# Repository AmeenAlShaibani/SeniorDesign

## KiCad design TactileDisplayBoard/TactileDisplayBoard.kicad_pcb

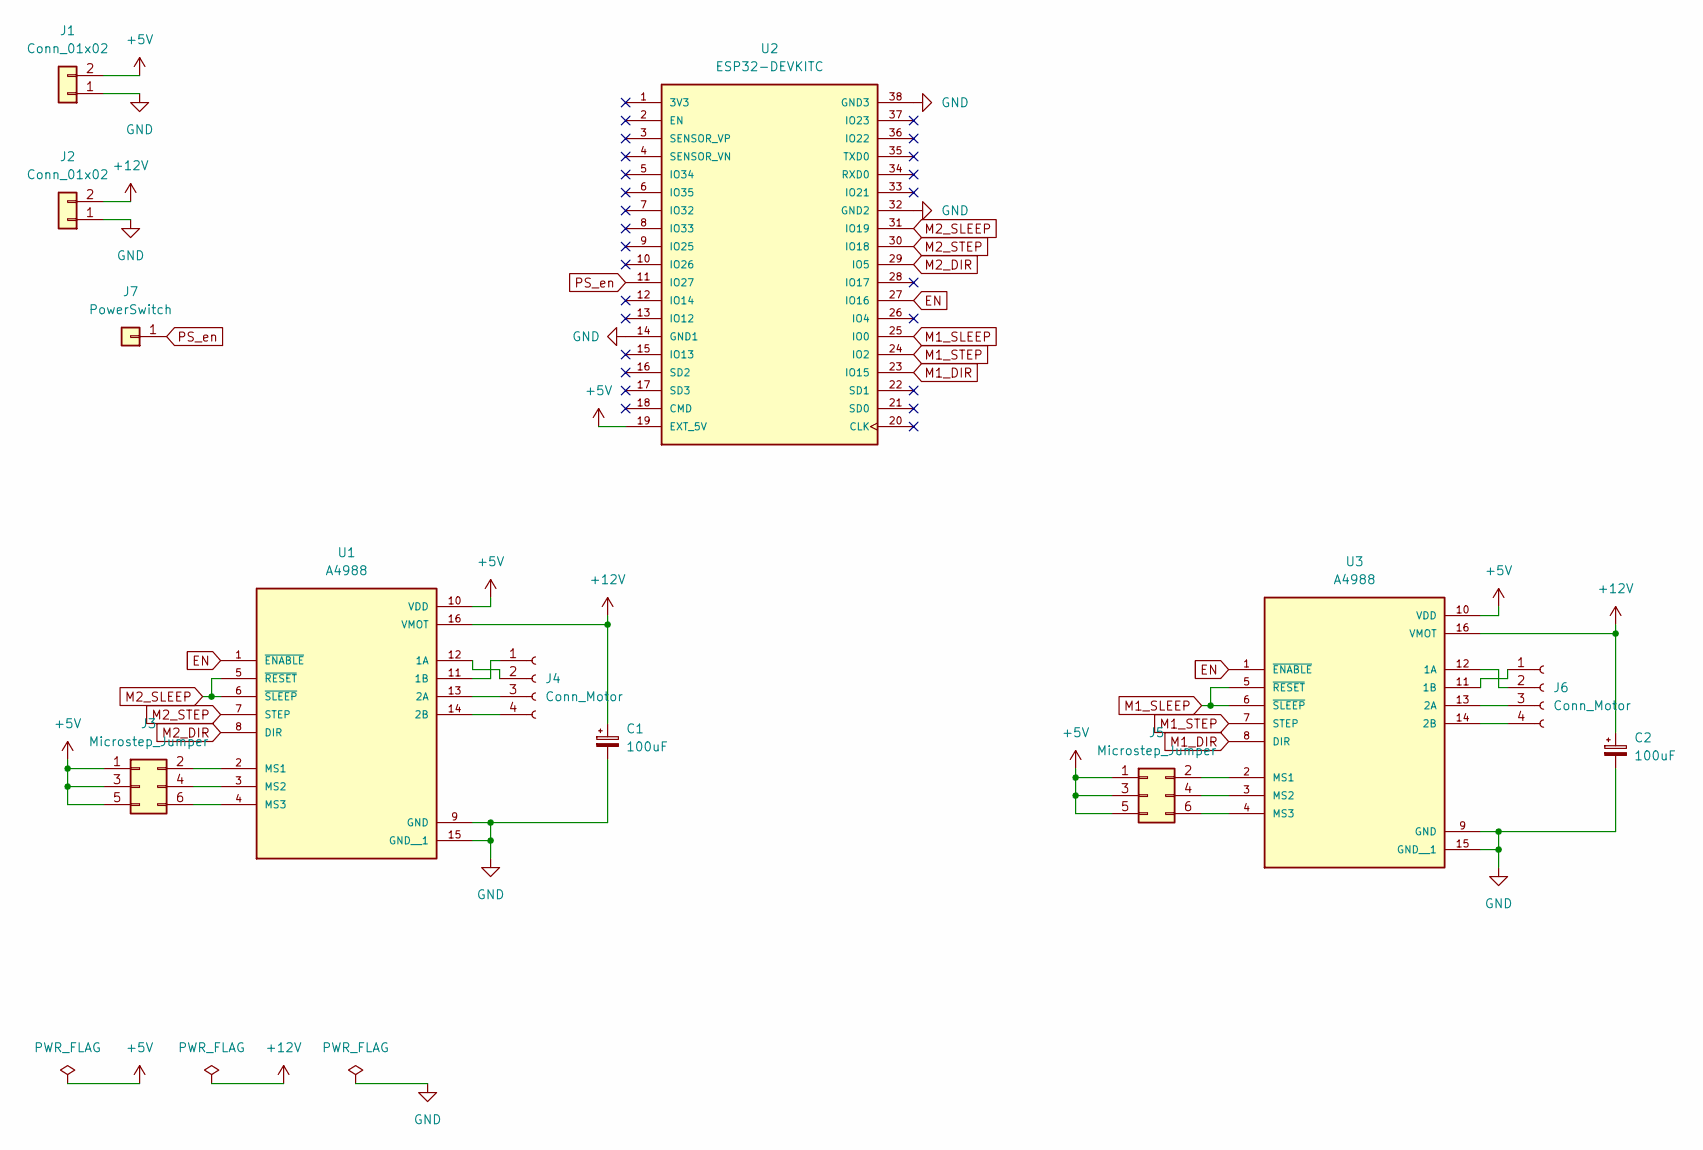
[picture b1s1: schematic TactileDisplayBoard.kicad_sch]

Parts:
C1, C2: 100uF; C_Radial_D10.0mm_H16.0mm_P5.00mm
J1, J2: Conn_01x02; BarrelJack_CUI_PJ-102AH_Horizontal
J3, J5: Microstep_Jumper; PinSocket_2x03_P2.54mm_Vertical
J4, J6: Conn_Motor; JST_XH_B4B-XH-A_1x04_P2.50mm_Vertical
J7: PowerSwitch; PinSocket_1x01_P2.54mm_Vertical
U1, U3: A4988; MODULE_A4988_STEPPER_MOTOR_DRIVER_CARRIER
U2: ESP32-DEVKITC; MODULE_ESP32-DEVKITC; PARTREV N/A

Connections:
+5V: J1.2, J3.1, J3.3, J3.5, J5.1, J5.3, J5.5, U1.10 (VDD), U2.19 (EXT_5V), U3.10 (VDD)
+12V: C1.1, C2.1, J2.2, U1.16 (VMOT), U3.16 (VMOT)
EN: U1.1 (~ENABLE), U2.27 (IO16), U3.1 (~ENABLE)
GND: C1.2, C2.2, J1.1, J2.1, U1.9 (GND), U1.15 (GND__1), U2.14 (GND1), U2.32 (GND2), U2.38 (GND3), U3.9 (GND), U3.15 (GND__1)
M1_DIR: U2.23 (IO15), U3.8 (DIR)
M1_SLEEP: U2.25 (IO0), U3.5 (~RESET), U3.6 (~SLEEP)
M1_STEP: U2.24 (IO2), U3.7 (STEP)
M2_DIR: U1.8 (DIR), U2.29 (IO5)
M2_SLEEP: U1.5 (~RESET), U1.6 (~SLEEP), U2.31 (IO19)
M2_STEP: U1.7 (STEP), U2.30 (IO18)
unnamed: J3.2, U1.2 (MS1)
unnamed: J3.4, U1.3 (MS2)
unnamed: J3.6, U1.4 (MS3)
unnamed: J4.1, U1.11 (1B)
unnamed: J4.2, U1.12 (1A)
unnamed: J4.3, U1.13 (2A)
unnamed: J4.4, U1.14 (2B)
unnamed: J5.2, U3.2 (MS1)
unnamed: J5.4, U3.3 (MS2)
unnamed: J5.6, U3.4 (MS3)
unnamed: J6.1, U3.11 (1B)
unnamed: J6.2, U3.12 (1A)
unnamed: J6.3, U3.13 (2A)
unnamed: J6.4, U3.14 (2B)
PS_en: J7.1, U2.11 (IO27)

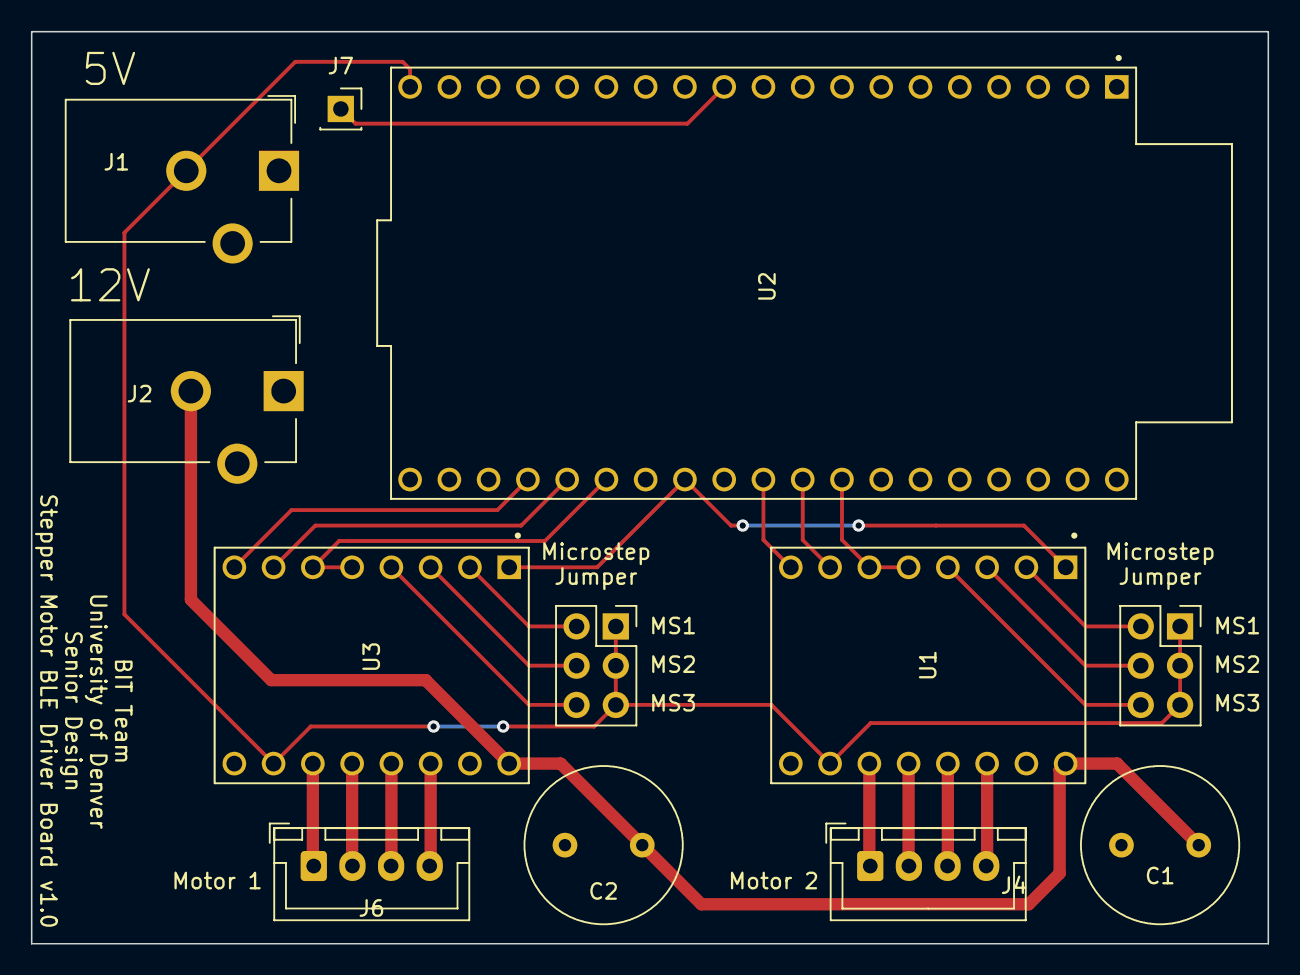
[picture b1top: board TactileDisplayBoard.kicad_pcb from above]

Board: 2 copper layers, 80.0 x 59.0 mm, 12 parts (0 on the bottom side), 25 nets.

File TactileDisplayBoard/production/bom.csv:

Designator,Footprint,Quantity,Value,LCSC Part #
"C1, C2",C_Radial_D10.0mm_H16.0mm_P5.00mm,2,100uF,
"J1, J2",BarrelJack_CUI_PJ-102AH_Horizontal,2,Conn_01x02,
"J3, J5",PinSocket_2x03_P2.54mm_Vertical,2,Microstep_Jumper,
"J4, J6",JST_XH_B4B-XH-A_1x04_P2.50mm_Vertical,2,Conn_Motor,
J7,PinSocket_1x01_P2.54mm_Vertical,1,PowerSwitch,
"U1, U3",MODULE_A4988_STEPPER_MOTOR_DRIVER_CARRIER,2,A4988,
U2,MODULE_ESP32-DEVKITC,1,ESP32-DEVKITC,

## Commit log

2023-04-27 Created Flipped version of the board
2023-04-28 Removed Legacy Trace
2023-05-19 Added BLE, and wrote firmware for ESP32 in Display Driver
2023-07-23 Adjusted wheel number and added shutoff system.
2023-10-02 Changed file naming, added all constants to configs.
